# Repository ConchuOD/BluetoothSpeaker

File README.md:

# Teensy Bluetooth Speaker           
This repo houses the hardware and code for a bluetooth speaker. It uses an [RN52 from Roving Networks](https://www.microchip.com/wwwproducts/en/RN52) on one daughterboard to provide the bluetooth streaming capabilities and a [Teensy3.2 from PJRC](https://www.pjrc.com/store/teensy32.html) on another to control operation and power a [touchscreen display](https://www.pjrc.com/store/display_ili9341_touch.html) which displays the song metadata as well as houses AVRCP buttons.
The amplification is provided by a [TI 20 Watt Class-D amplifier](http://www.ti.com/lit/ds/symlink/tpa3140d2.pdf). Power comes from a 3S LiPo battery I had lying around from a RC project, with the amp being powered from 10.5 volts & seperate 3.3V rail for the RN52/Teensy/Display.

The V1 board only worked after a number of modifications were made. These modifications were echoed in V2 which also introduced the display. A V3 is planned which will place the RN52 directly on the board itself. As the RN52 is relatively expensive the V1/V2 boards were created with the option to use a cheap Chinese A2DP module which required swapping the ADP2370 for an adjustable version as well as inserting some zero Ohm links. An approximate BOM is included as a spreadsheet, however the pricing in the first section is all rather approximate.

*>insert photos of display, board & enclosure when complete*

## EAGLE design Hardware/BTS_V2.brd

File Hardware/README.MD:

# BTS - unfinished                 
Nothing in here is even confirmed to function correctly yet - in fact I would more likely guarantee failure.                 
As things can actually be tested the corresponding parts of the repo. will be updated.

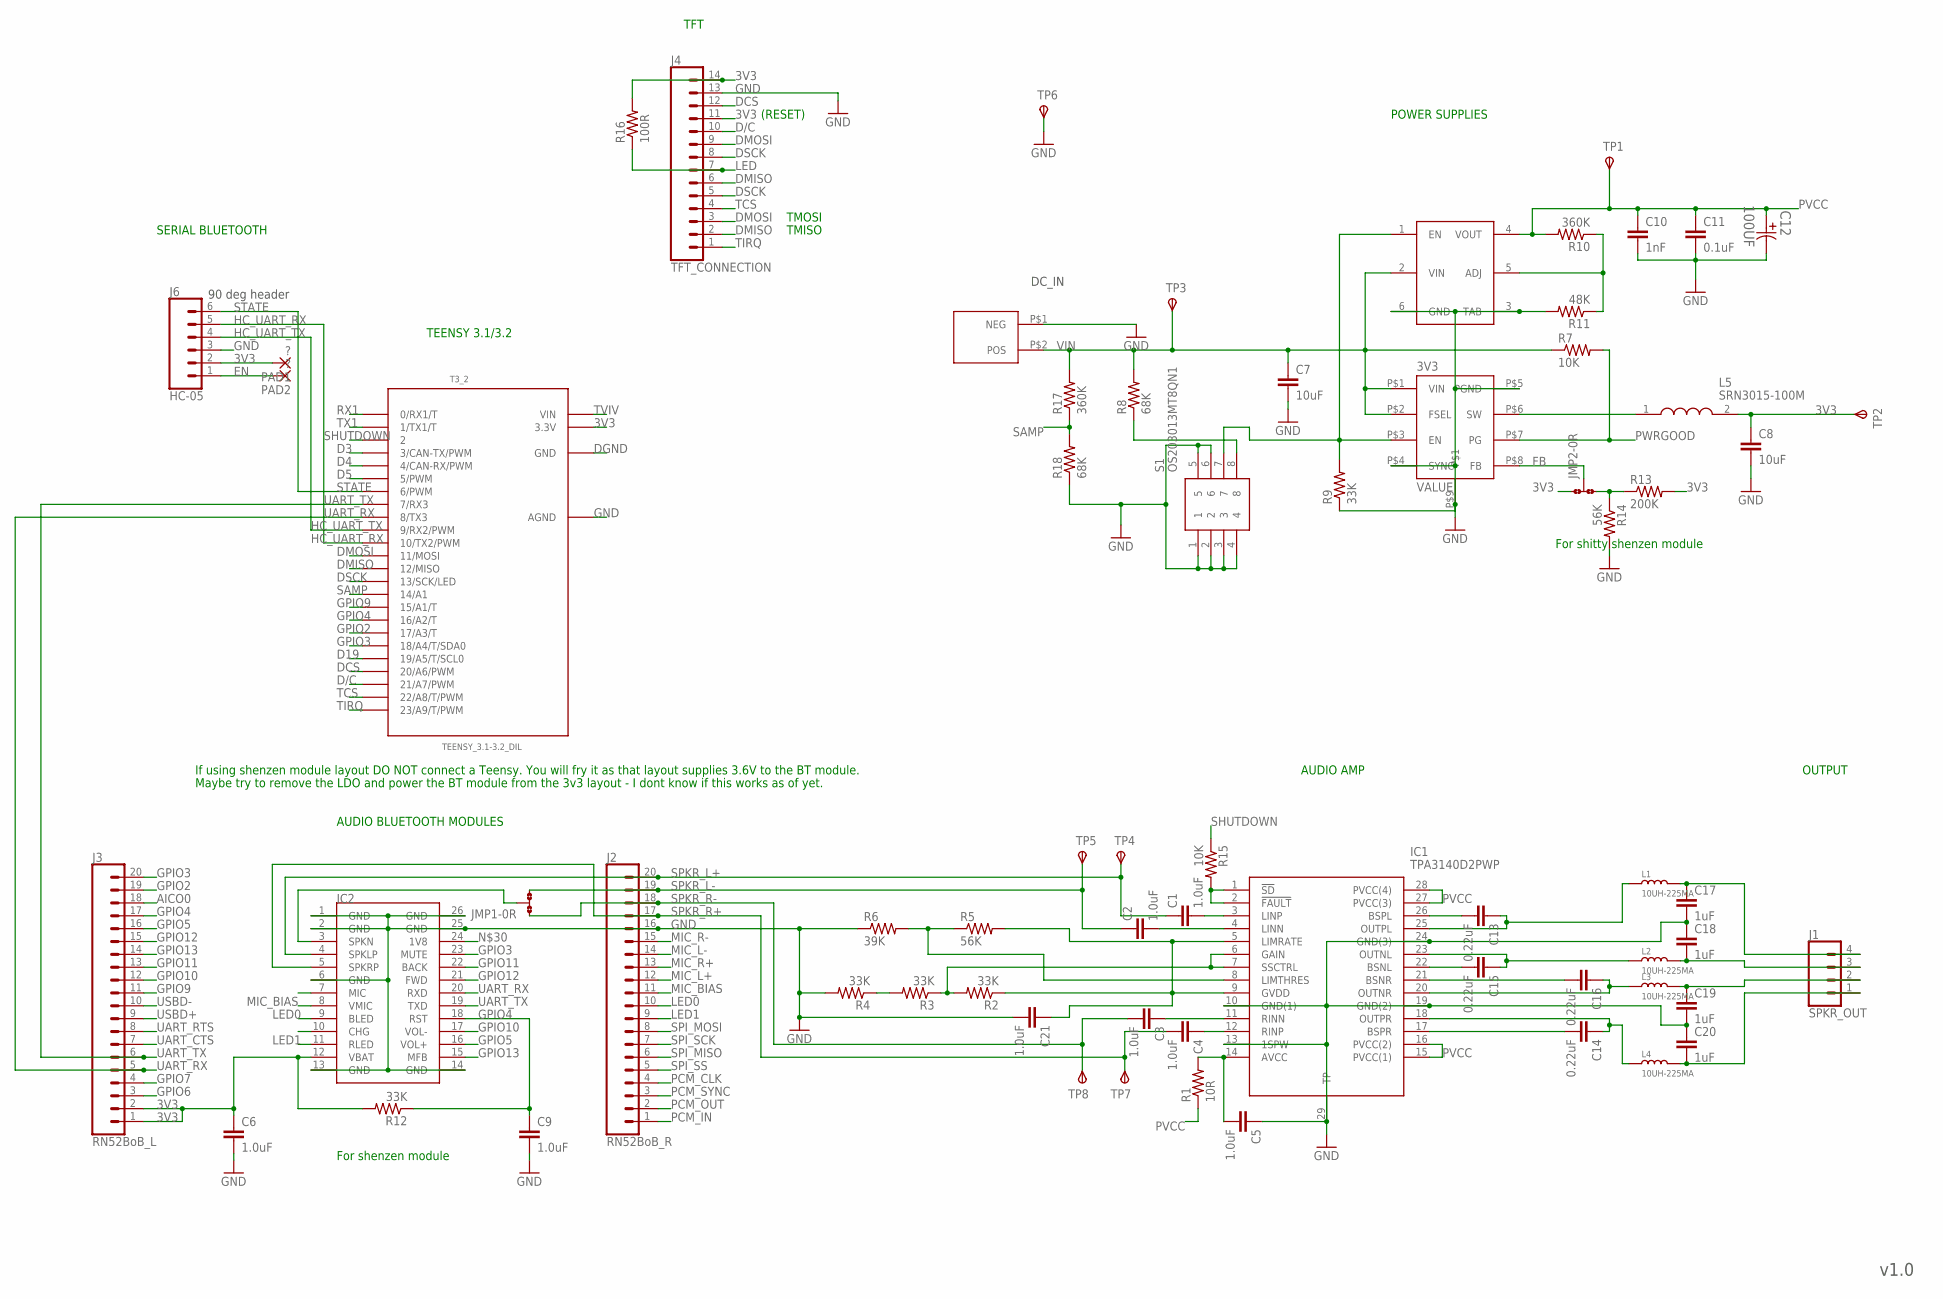
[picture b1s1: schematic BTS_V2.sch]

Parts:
3V3: ADP2370; 3MM_LFCSP_QFN
C1, C2, C3, C4, C5, C6, C9, C21: 1.0uF; 0603
C7, C8: 10uF; C3216
C10: 1nF; 0603
C11: 0.1uF; 0603
C12: 100UF; CAPAE660X610N
C13, C14, C15, C16: 0.22uF; 0603
C17, C18, C19, C20: 1uF; 0603
IC1: TPA3140D2PWP; SOP65P640X120-29N
IC2: BLK-MD-SPK-B
J1: SPKR_OUT; SCREWTERMINAL-3.5MM-4
J2: RN52BoB_R; 1X20
J3: RN52BoB_L; 1X20
J4: TFT_CONNECTION; 1X14
J6: HC-05; 1X06
JMP1, JMP2: 0R-JUMPA; A0R-JMP
L1, L2, L3, L4: 10UH-225MA; L0806
L5: SRN3015-100M; SRN3015
PAD1, PAD2: ?; SMD1,27-2,54
R1: 10R; R0603
R2, R3, R4, R9, R12: 33K; R0603
R5, R14: 56K; R0603
R6: 39K; R0603
R7, R15: 10K; R0603
R8, R18: 68K; R0603
R10, R17: 360K; R0603
R11: 48K; R0603
R13: 200K; R0603
R16: 100R; R0603
S1: OS203013MT8QN1
T3_2: TEENSY_3.1-3.2_DIL; TEENSY_3.0-3.2&LC_DIL
TP1, TP2, TP3, TP4, TP5, TP6, TP7, TP8: TPSPAD1-17; P1-17
U$1: HK_XT-60; HOBBYKING_XT-60
U$2: NCP59302; D2PAK-5

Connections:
3V3: C6.1, C8.1, IC2.12 (VBAT), J3.1, J3.2, J4.11, J4.14, J6.2, JMP2.1, L5.2, PAD1.1, R12.2, R13.2, R16.2, T3_2.3.3V, TP2.TP
AICO0: J3.18
BSNL: C15.2, IC1.22 (BSNL)
BSNR: C16.2, IC1.21 (BSNR)
BSPL: C13.2, IC1.26 (BSPL)
BSPR: C14.2, IC1.17 (BSPR)
D3: T3_2.3 (3/CAN-TX/PWM)
D4: T3_2.4 (4/CAN-RX/PWM)
D5: T3_2.5 (5/PWM)
D19: T3_2.19/A5 (19/A5/T/SCL0)
D/C: J4.10, T3_2.21/A7 (21/A7/PWM)
DCS: J4.12, T3_2.20/A6 (20/A6/PWM)
DGND: T3_2.GND
DMISO: J4.2, J4.6, T3_2.12 (12/MISO)
DMOSI: J4.3, J4.9, T3_2.11 (11/MOSI)
DSCK: J4.5, J4.8, T3_2.13 (13/SCK/LED)
EN: J6.1, PAD2.1
FB: 3V3.P$8 (FB), JMP2.2
GAIN: IC1.6 (GAIN), IC1.7 (SSCTRL), R2.2, R3.1
GND: 3V3.P$4 (SYNC), 3V3.P$5 (PGND), 3V3.P$9, C5.1, C6.2, C7.2, C8.2, C9.2, C10.2, C11.2, C12.2, C17.2, C18.1, C19.2, C20.1, C21.2, IC1.10 (GND(1)), IC1.13 (1SPW), IC1.19 (GND(2)), IC1.24 (GND(3)), IC1.29 (TP), IC2.1 (GND), IC2.2 (GND), IC2.6 (GND), IC2.13 (GND), IC2.14 (GND), IC2.25 (GND), IC2.26 (GND), J2.16, J4.13, J6.3, R4.2, R6.1, R9.1, R11.2, R14.2, R18.1, S1.1, S1.2, S1.3, S1.4, S1.5, S1.6, T3_2.AGND, TP6.TP, U$1.P$1 (NEG), U$2.3 (TAB), U$2.6 (GND)
GPIO2: J3.19, T3_2.17/A3 (17/A3/T)
GPIO3: IC2.23 (MUTE), J3.20, T3_2.18/A4 (18/A4/T/SDA0)
GPIO4: C9.1, IC2.18 (RST), J3.17, R12.1, T3_2.16/A2 (16/A2/T)
GPIO5: IC2.16 (VOL+), J3.16
GPIO6: J3.3
GPIO7: J3.4
GPIO9: J3.11, T3_2.15/A1 (15/A1/T)
GPIO10: IC2.17 (VOL-), J3.12
GPIO11: IC2.22 (BACK), J3.13
GPIO12: IC2.21 (FWD), J3.15
GPIO13: IC2.15 (MFB), J3.14
GVDD: C21.1, IC1.5 (LIMRATE), IC1.9 (GVDD), R2.1, R5.2
HC_UART_RX: J6.5, T3_2.10 (10/TX2/PWM)
HC_UART_TX: J6.4, T3_2.9 (9/RX2/PWM)
LED: J4.7, R16.1
LED0: IC2.9 (BLED), J2.10
LED1: IC2.11 (RLED), J2.9
LIMTHRES: IC1.8 (LIMTHRES), R5.1, R6.2
LINN: C2.2, IC1.4 (LINN)
LINP: C1.2, IC1.3 (LINP)
MIC_BIAS: IC2.8 (VMIC), J2.11
MIC_L+: J2.12
MIC_L-: J2.14
MIC_R+: J2.13
MIC_R-: J2.15
unnamed: C5.2, IC1.14 (AVCC), R1.2
unnamed: IC1.1 (!SD), IC1.2 (!FAULT), R15.2
unnamed: R3.2, R4.1
unnamed: C17.1, J1.4, L1.2
unnamed: C18.2, J1.3, L2.2
unnamed: C19.1, J1.2, L3.2
unnamed: C20.2, J1.1, L4.2
unnamed: JMP2.3, R13.1, R14.1
unnamed: IC2.3 (SPKN), JMP1.2
unnamed: 3V3.P$3 (EN), R9.2, S1.7, U$2.1 (EN)
unnamed: 3V3.P$6 (SW), L5.1
unnamed: R8.1, S1.8
unnamed: R10.1, R11.1, U$2.5 (ADJ)
OUTNL: C15.1, IC1.23 (OUTNL), L2.1
OUTNR: C16.1, IC1.20 (OUTNR), L3.1
OUTPL: C13.1, IC1.25 (OUTPL), L1.1
OUTPR: C14.1, IC1.18 (OUTPR), L4.1
PCM_CLK: J2.4
PCM_IN: J2.1
PCM_OUT: J2.2
PCM_SYNC: J2.3
PVCC: C10.1, C11.1, C12.1, IC1.15 (PVCC(1)), IC1.16 (PVCC(2)), IC1.27 (PVCC(3)), IC1.28 (PVCC(4)), R1.1, R10.2, TP1.TP, U$2.4 (VOUT)
PWRGOOD: 3V3.P$7 (PG), R7.2
RINN: C3.1, IC1.11 (RINN)
RINP: C4.1, IC1.12 (RINP)
RX1: T3_2.0 (0/RX1/T)
SAMP: R17.1, R18.2, T3_2.14/A0 (14/A1)
SHUTDOWN: R15.1, T3_2.2
SPI_MISO: J2.6
SPI_MOSI: J2.8
SPI_SCK: J2.7
SPI_SS: J2.5
SPKR_L+: C1.1, IC2.4 (SPKLP), J2.20, TP4.TP
SPKR_L-: C2.1, J2.19, JMP1.3, TP5.TP
SPKR_R+: C4.2, IC2.5 (SPKRP), J2.17, TP7.TP
SPKR_R-: C3.2, J2.18, JMP1.1, TP8.TP
STATE: J6.6, T3_2.6 (6/PWM)
TCS: J4.4, T3_2.22/A8 (22/A8/T/PWM)
TIRQ: J4.1, T3_2.23/A9 (23/A9/T/PWM)
TVIV: T3_2.VIN
TX1: T3_2.1 (1/TX1/T)
UART_CTS: J3.7
UART_RTS: J3.8
UART_RX: IC2.20 (RXD), J3.5, T3_2.8 (8/TX3)
UART_TX: IC2.19 (TXD), J3.6, T3_2.7 (7/RX3)
USBD+: J3.9
USBD-: J3.10
VIN: 3V3.P$1 (VIN), 3V3.P$2 (FSEL), C7.1, R7.1, R8.2, R17.2, TP3.TP, U$1.P$2 (POS), U$2.2 (VIN)

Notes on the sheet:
For shenzen module
For shitty shenzen module
DC_IN
90 deg header
If using shenzen module layout DO NOT connect a Teensy. You will fry it as that layout supplies 3.6V to the BT module.
v1.0
(RESET)
TMOSI
TMISO
Maybe try to remove the LDO and power the BT module from the 3v3 layout - I dont know if this works as of yet.
TFT
POWER SUPPLIES
AUDIO AMP
OUTPUT
AUDIO BLUETOOTH MODULES
SERIAL BLUETOOTH
TEENSY 3.1/3.2

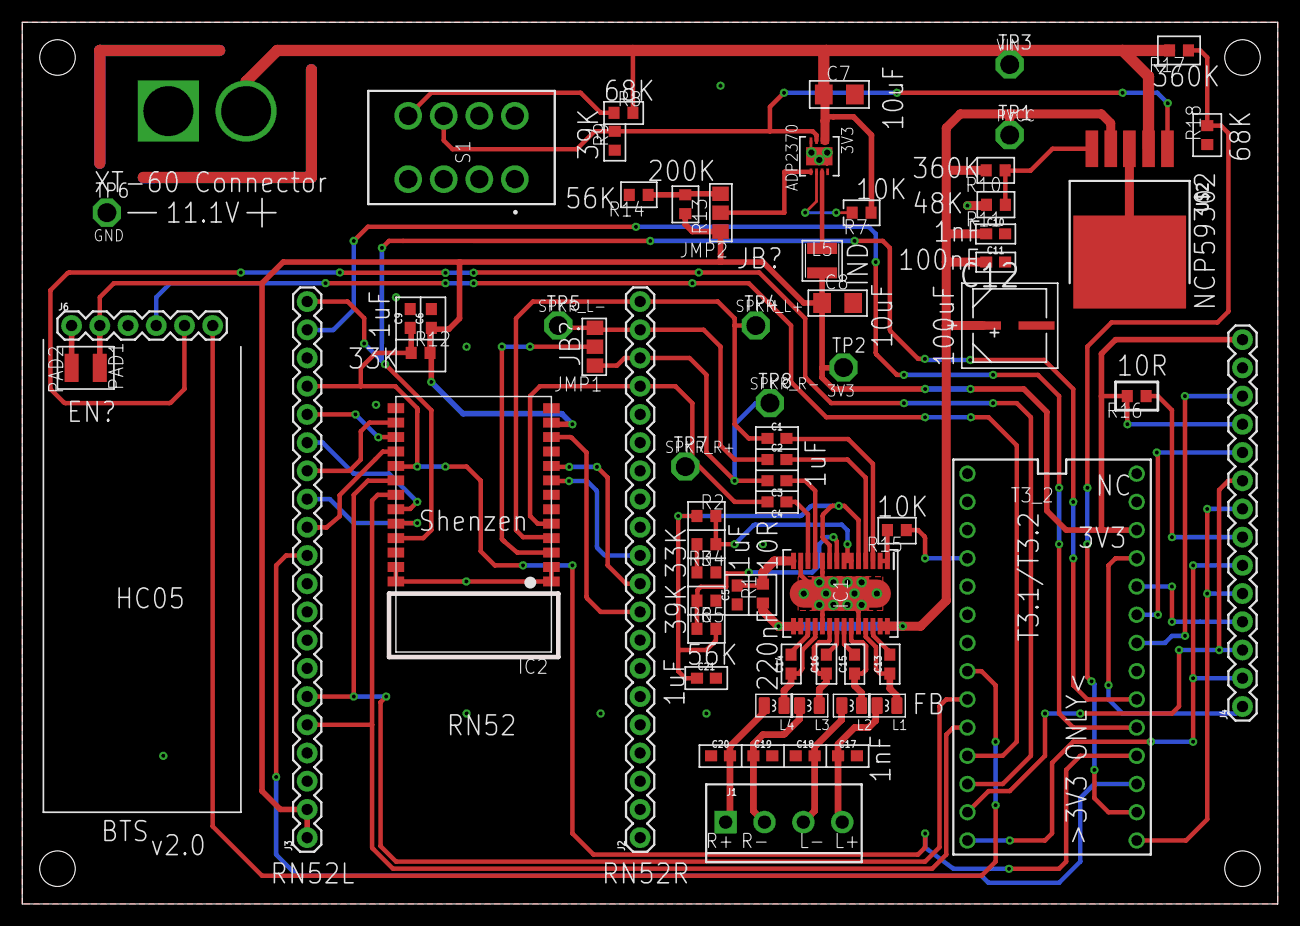
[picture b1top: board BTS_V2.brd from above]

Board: 2 copper layers, 112.6 x 79.0 mm, 68 parts (0 on the bottom side), 66 nets.

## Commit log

2018-02-26 v1.0 for PCB fabrication
2018-02-26 tPlace additions
2018-03-14 Initial code - compilation not attempted
2018-03-14 Moved hardware files
2018-03-15 Finally fixed?
2018-03-21 XT60 connects still wrong size
2018-03-21 Deleted duplicate directory
2018-03-21 XT-60 connects still wrong size
2018-03-21 rename
2018-03-21 Functionality added, still untested
2018-03-21 Slight change
2018-03-22 on second thoughts...
2018-03-23 oops
2018-03-26 Created new XT-60 connector
2018-03-28 added PA test code & modified V2 board files
2018-03-28 Readme and ARDUINO IDE required changes
2018-03-28 Further error fixed
2018-03-28 Error actually fixed
2018-03-28 Expanding on the BTS code
2018-03-28 Finished for today
2018-03-28 one word
2018-03-29 Submodules
2018-03-29 Hardware submodule
2018-03-29 Submodule update.
2018-03-29 trying to get a functional makefile
2018-03-29 Makefile issue hopefully fixed
2018-03-29 Makefile fixed/code compiled. Not run yet
2018-03-30 Removed examples from SPI lib
2018-03-30 More Makefile fiddling
2018-04-03 Board errors corrected
2018-04-10 Still working on figuring out an error w/ the board
2018-04-10 still tracking down issue
2018-04-22 Finally solved the issue - was a too large cap on output
2018-04-26 Fixed a major and minor Makefile issues and general fixes in BTS.cpp
2018-04-26 Adding code TODO
2018-04-26 updating RN52 lib
2018-04-26 fixing merge artifact
2018-04-27 Finally got it to compile and run though audio not checked
2018-04-28 Ready to test screen.
2018-04-28 Fixed copyright
2018-05-03 variable names & board v2 for manuf.
2018-05-03 TODO change
2018-05-22 added untested touch code
2018-05-22 adding touch controller library
2018-05-22 formatting
2018-05-22 ToDo
2018-05-27 Bug fixing for display
2018-05-29 TFT, touch and RN52 updates
2018-05-29 Removing unused fonts - storage rejoices!
2018-05-29 README.md
2018-05-29 Fixed a time display bug & word overlaps
2018-05-30 bug huntin
2018-06-02 fixing time update code
2018-06-02 more bug fixes
2018-06-02 Fixed two HW issues
2018-06-02 images
2018-06-02 image
2018-06-02 Starting to use button bitmaps
2018-06-02 image things
2018-06-02 added all bitmaps
2018-06-02 BITMAP BUTTONS, AYYYO
2018-06-03 touch stll doesnt work
2018-06-04 Correct touch controller
2018-06-04 Correct folder name
2018-06-04 Code seems to work in totality
2018-06-04 Sorting out ?s
2018-06-06 removed unneeded variables. Hopefully broke nothing
2018-06-06 submodule update
2018-06-06 DEBUG mode off
2018-06-07 BOM update
2018-06-09 updating AmpTest
2018-06-09 README update
2018-06-21 Adding LVC shutdown code
2019-12-10 Updating rn52 breakout to one with saved gerbers
2022-05-22 Create LICENSE

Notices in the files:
parts and their libraries:
SparkFun-Capacitors: Licensing: Creative Commons ShareAlike 4.0 International - https://creativecommons.org/licenses/by-sa/4.0
